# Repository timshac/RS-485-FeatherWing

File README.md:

# RS-485-FeatherWing
RS-485 FeatherWing

Can be used with any Feather style microcontroller

Firmware and simple mobile app available for Particle Argon or Boron microcontroller.

Connect your modbus client unit to your phone using the Particle.io mobile app.

Control your chiller or process heat from your phone.

## Use Scenario

* RS-485 Featherwing ([github](https://github.com/timshac/RS-485-FeatherWing), [tindie](https://www.tindie.com/products/hudsonsonoma/rs-485-modbus-controller-with-mobile-app/))
* Particle Argon or Boron ([purchase](https://store.particle.io/collections/gen-3))

## Building the Hardware

Clone this repository. Use Kicad to edit the circuit board and generate gerbers, or send the existing Gerbers to a fab. I use Seeed Studio.
Use the BOM to order parts.

## Connect hardware

1. Wire the RS-485 Featherwing to your modbus RTU unit.  Connect D1 <-> A and D2 <-> B
Power the RS-485 Featherwing with 5.2-36v DC (200mA)
2. Insert the Boron or Argon into the RS-485 Featherwing
3. Connnect particle Boron (Cellular) or Argon (WiFi) to the Particle cloud using the Particle mobile app: [Android](https://play.google.com/store/apps/details?id=io.particle.android.app), [iOS](https://apps.apple.com/us/app/particle-iot/id991459054)

## Demo Firmware available

Clone this firmware
[Github Novus-N322-modbus-RTU-driver](https://github.com/timshac/Novus-N322-modbus-RTU-driver)
Adapt to your modbus RTU device

## Example Particle.io Mobile App

For the demo firmware

## Let's talk - Office Hours

Are you interested in this system of tools we are building? 

I would love to talk and listen to you!

Please book a free 20 minute session - [Hudson Sonoma Office Hours](https://calendly.com/twbishop/hudson-sonoma-office-hours) - if you would like to talk about any of the following:

* Understanding what this is and why it might be useful for you
* Customizing the firmware or mobile app
* Feedback having used (or tried to use) this product

## License

* Hardware: CERN-OHL-P

This hardware is intended for further engineering and/or development, it is not an end user product. This development product is supplied AS IS, without any warranties, with all faults, at the buyer’s and further users’ sole risk. The user assumes all responsibility and liability for proper and safe operation.

The user understands and agrees that this is not designed for use in safety-critical applications where a failure of the product would reasonably be expected to cause severe personal injury or death.

Any use of this firmware and/or hardware is solely at the customer’s risk, and that customer is solely responsible for compliance with all legal and regulatory requirements in connection with such use.

HARDWARE AND ANY RELATED SOFTWARE IS PROVIDED ‘AS IS’ WITH NO ADDITIONAL WARRANTY.

THERE IS NO OTHER WARRANTY, EXPRESS OR IMPLIED, SUCH AS WARRANTY OF MERCHANTABILITY, FITNESS FOR PARTICULAR PURPOSE OR NON INFRINGEMENT.

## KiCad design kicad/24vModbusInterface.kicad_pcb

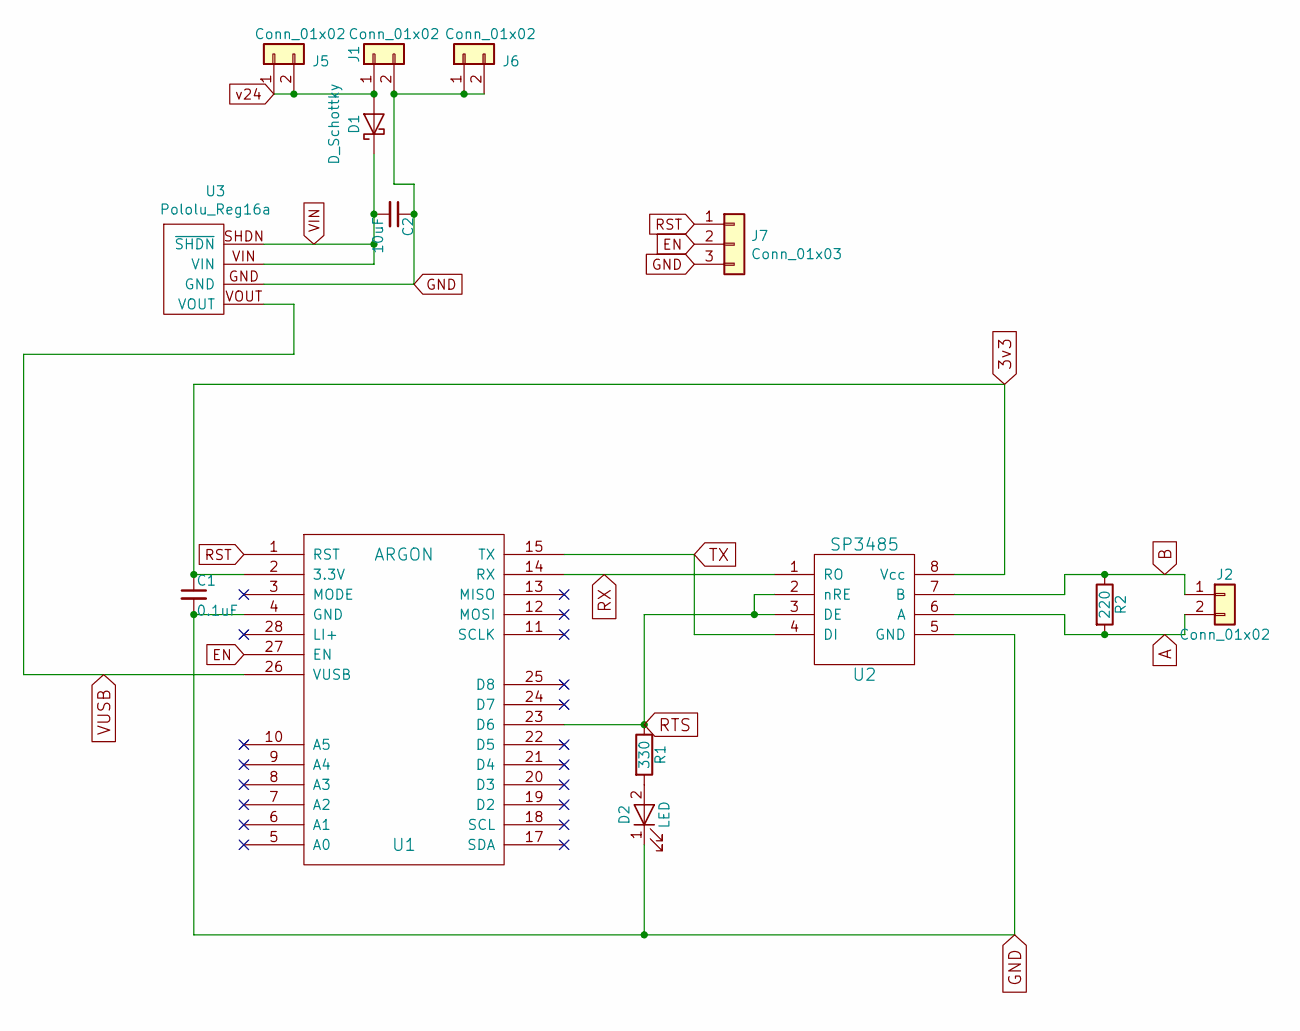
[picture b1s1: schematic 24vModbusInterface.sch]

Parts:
C1: 0.1uF; C_0603_HandSoldering
C2: 10uF; C_0805_HandSoldering
D1: D_Schottky; D_SOD-323_HandSoldering
D2: LED; LED_0603_HandSoldering
J1, J2: Conn_01x02; TerminalBlock_Pheonix_PT-3.5mm_2pol
J5, J6: Conn_01x02; TerminalBlock_Phoenix_PT-1,5-2-3.5-H_1x02_P3.50mm_Horizontal
J7: Conn_01x03; TerminalBlock_Phoenix_PT-1,5-3-3.5-H_1x03_P3.50mm_Horizontal
R1: 330; R_0603_HandSoldering
R2: 220; R_0603_HandSoldering
U1: ARGON; FeatherWing
U2: SP3485; SOIC-8_3.9x4.9mm_Pitch1.27mm
U3: Pololu_Reg16a; Pololu_reg16a

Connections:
3v3: C1.1, U1.2 (3.3V), U2.8 (Vcc)
A: J2.2, R2.2, U2.6 (A)
B: J2.1, R2.1, U2.7 (B)
EN: J7.2, U1.27 (EN)
GND: C1.2, C2.1, D2.1 (K), J1.2, J6.1, J6.2, J7.3, U1.4 (GND), U2.5 (GND), U3.GND
unnamed: D2.2 (A), R1.2
RST: J7.1, U1.1 (RST)
RTS: R1.1, U1.23 (D6), U2.2 (nRE), U2.3 (DE)
RX: U1.14 (RX), U2.1 (RO)
TX: U1.15 (TX), U2.4 (DI)
VIN: C2.2, D1.1 (K), U3.SHDN (~SHDN), U3.VIN
VUSB: U1.26 (VUSB), U3.VOUT
v24: D1.2 (A), J1.1, J5.1, J5.2

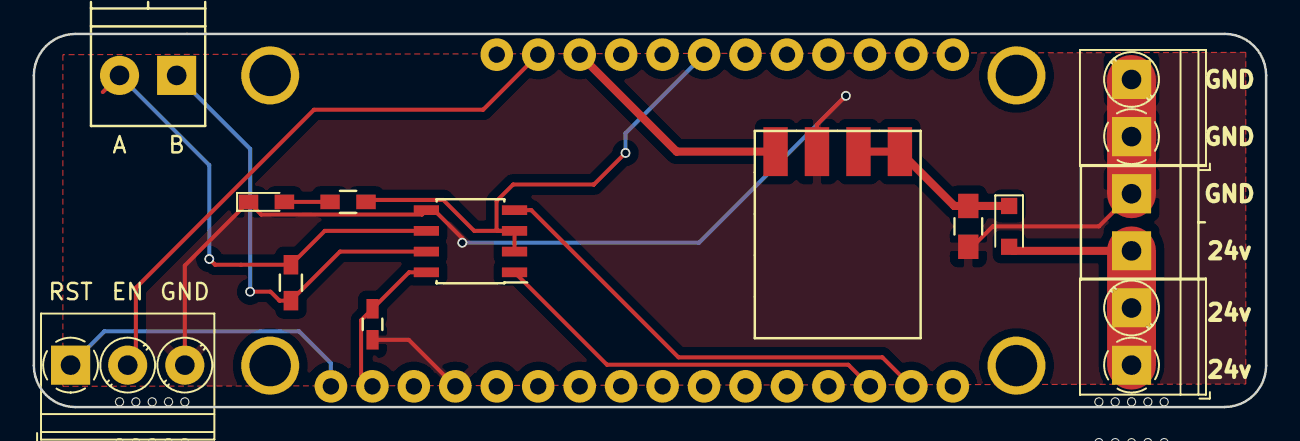
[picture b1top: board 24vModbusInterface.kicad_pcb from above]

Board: 2 copper layers, 75.5 x 22.9 mm, 15 parts (0 on the bottom side), 13 nets.

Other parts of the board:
PCB**: VAL**; PCB_FeatherWing_4hole

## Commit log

2021-03-06 files
2021-03-06 license
2021-03-06 fix case
2021-03-06 Office Hours
2021-04-23 CERN-OHL-P
2021-04-23 detail license

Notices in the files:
kicad/24vModbusInterface.kicad_pcb:
(c) 2020
